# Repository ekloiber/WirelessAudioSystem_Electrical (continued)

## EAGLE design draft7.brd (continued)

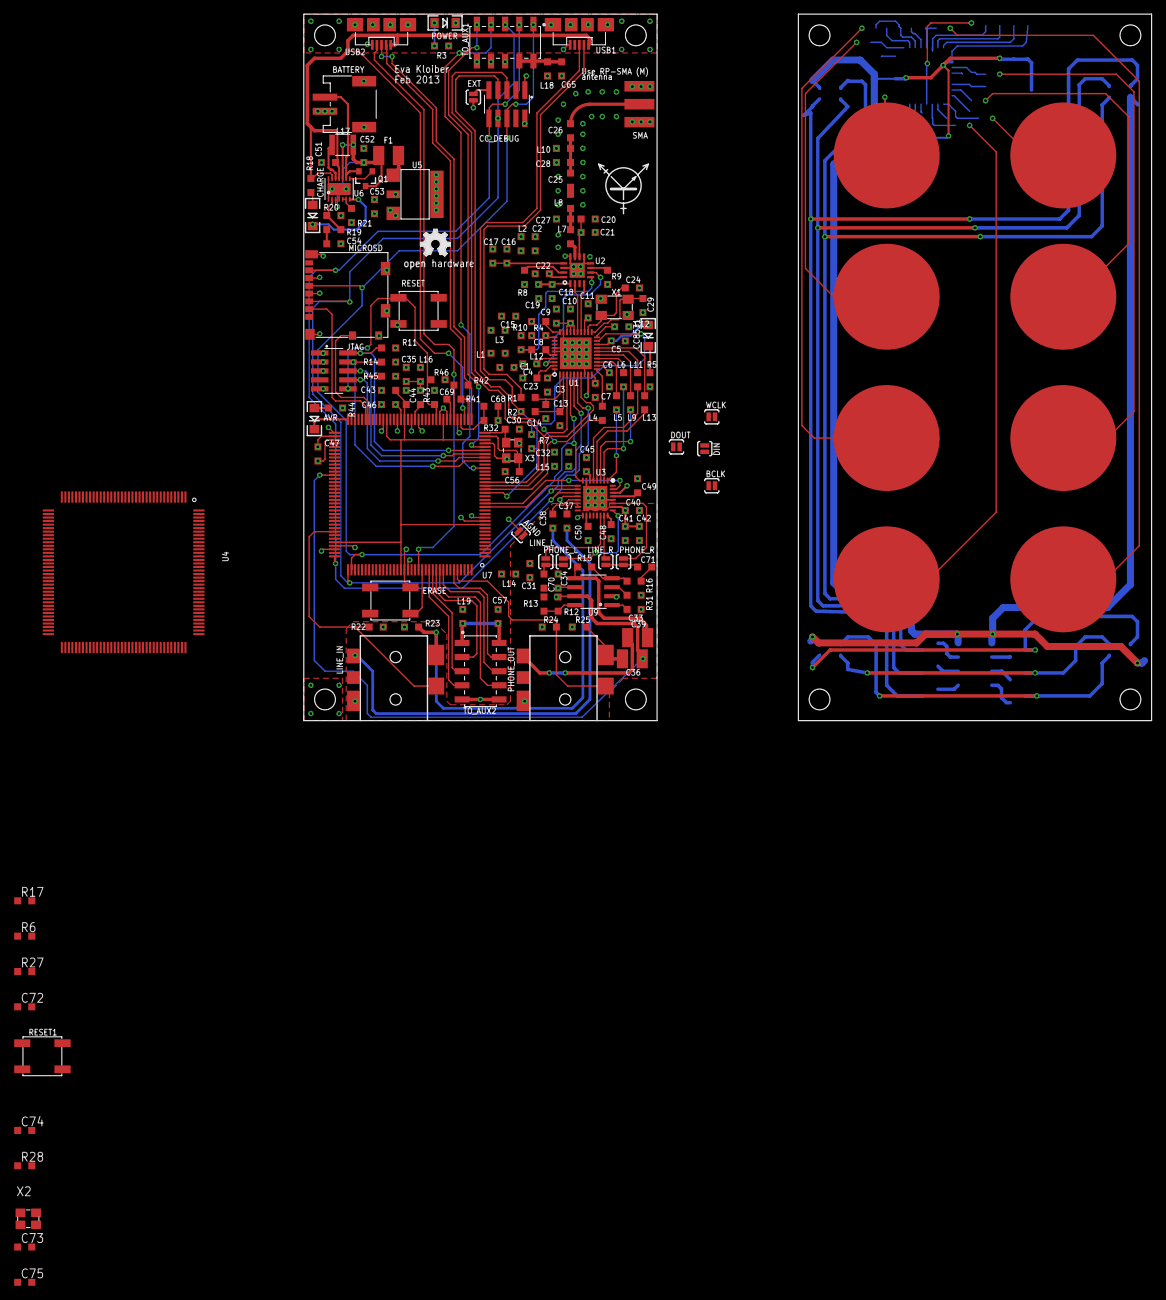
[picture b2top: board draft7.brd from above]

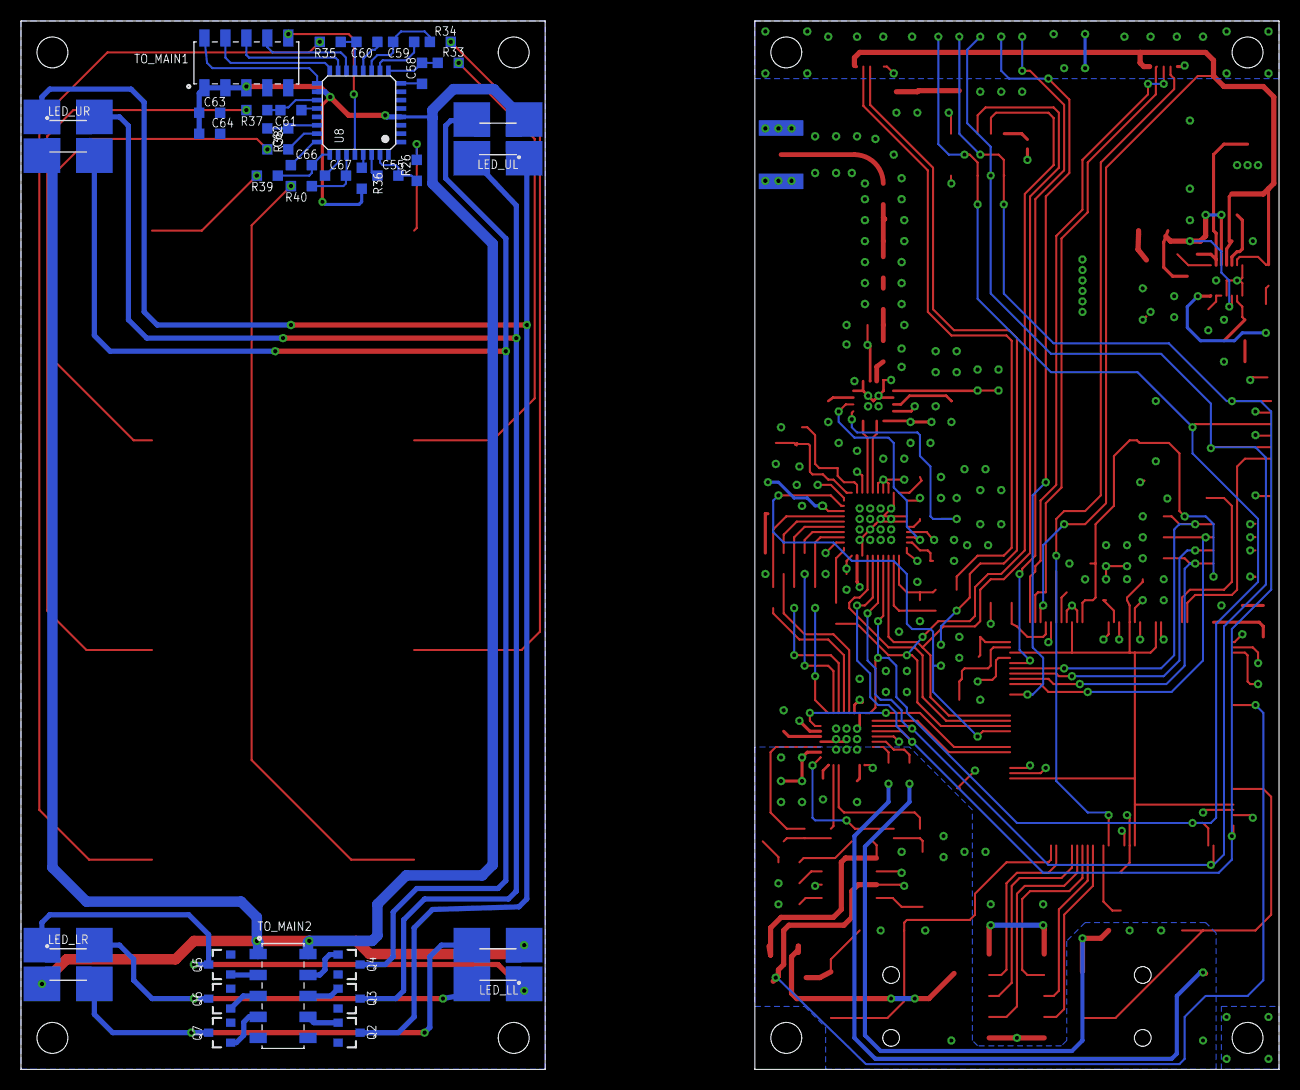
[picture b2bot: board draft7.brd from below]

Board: 4 copper layers, 120.0 x 100.0 mm, 214 parts (32 on the bottom side), 173 nets.

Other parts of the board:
U$1, U$5, U$6, U$7, U$8, U$11, U$12, U$13: STANDOFF_3/16
U$2, U$3: PHONE_PLUG
U$4, U$14: UBBP01
U$9: TRANS_SILK
U$10: OSHW_FILLX150_NOTEXT

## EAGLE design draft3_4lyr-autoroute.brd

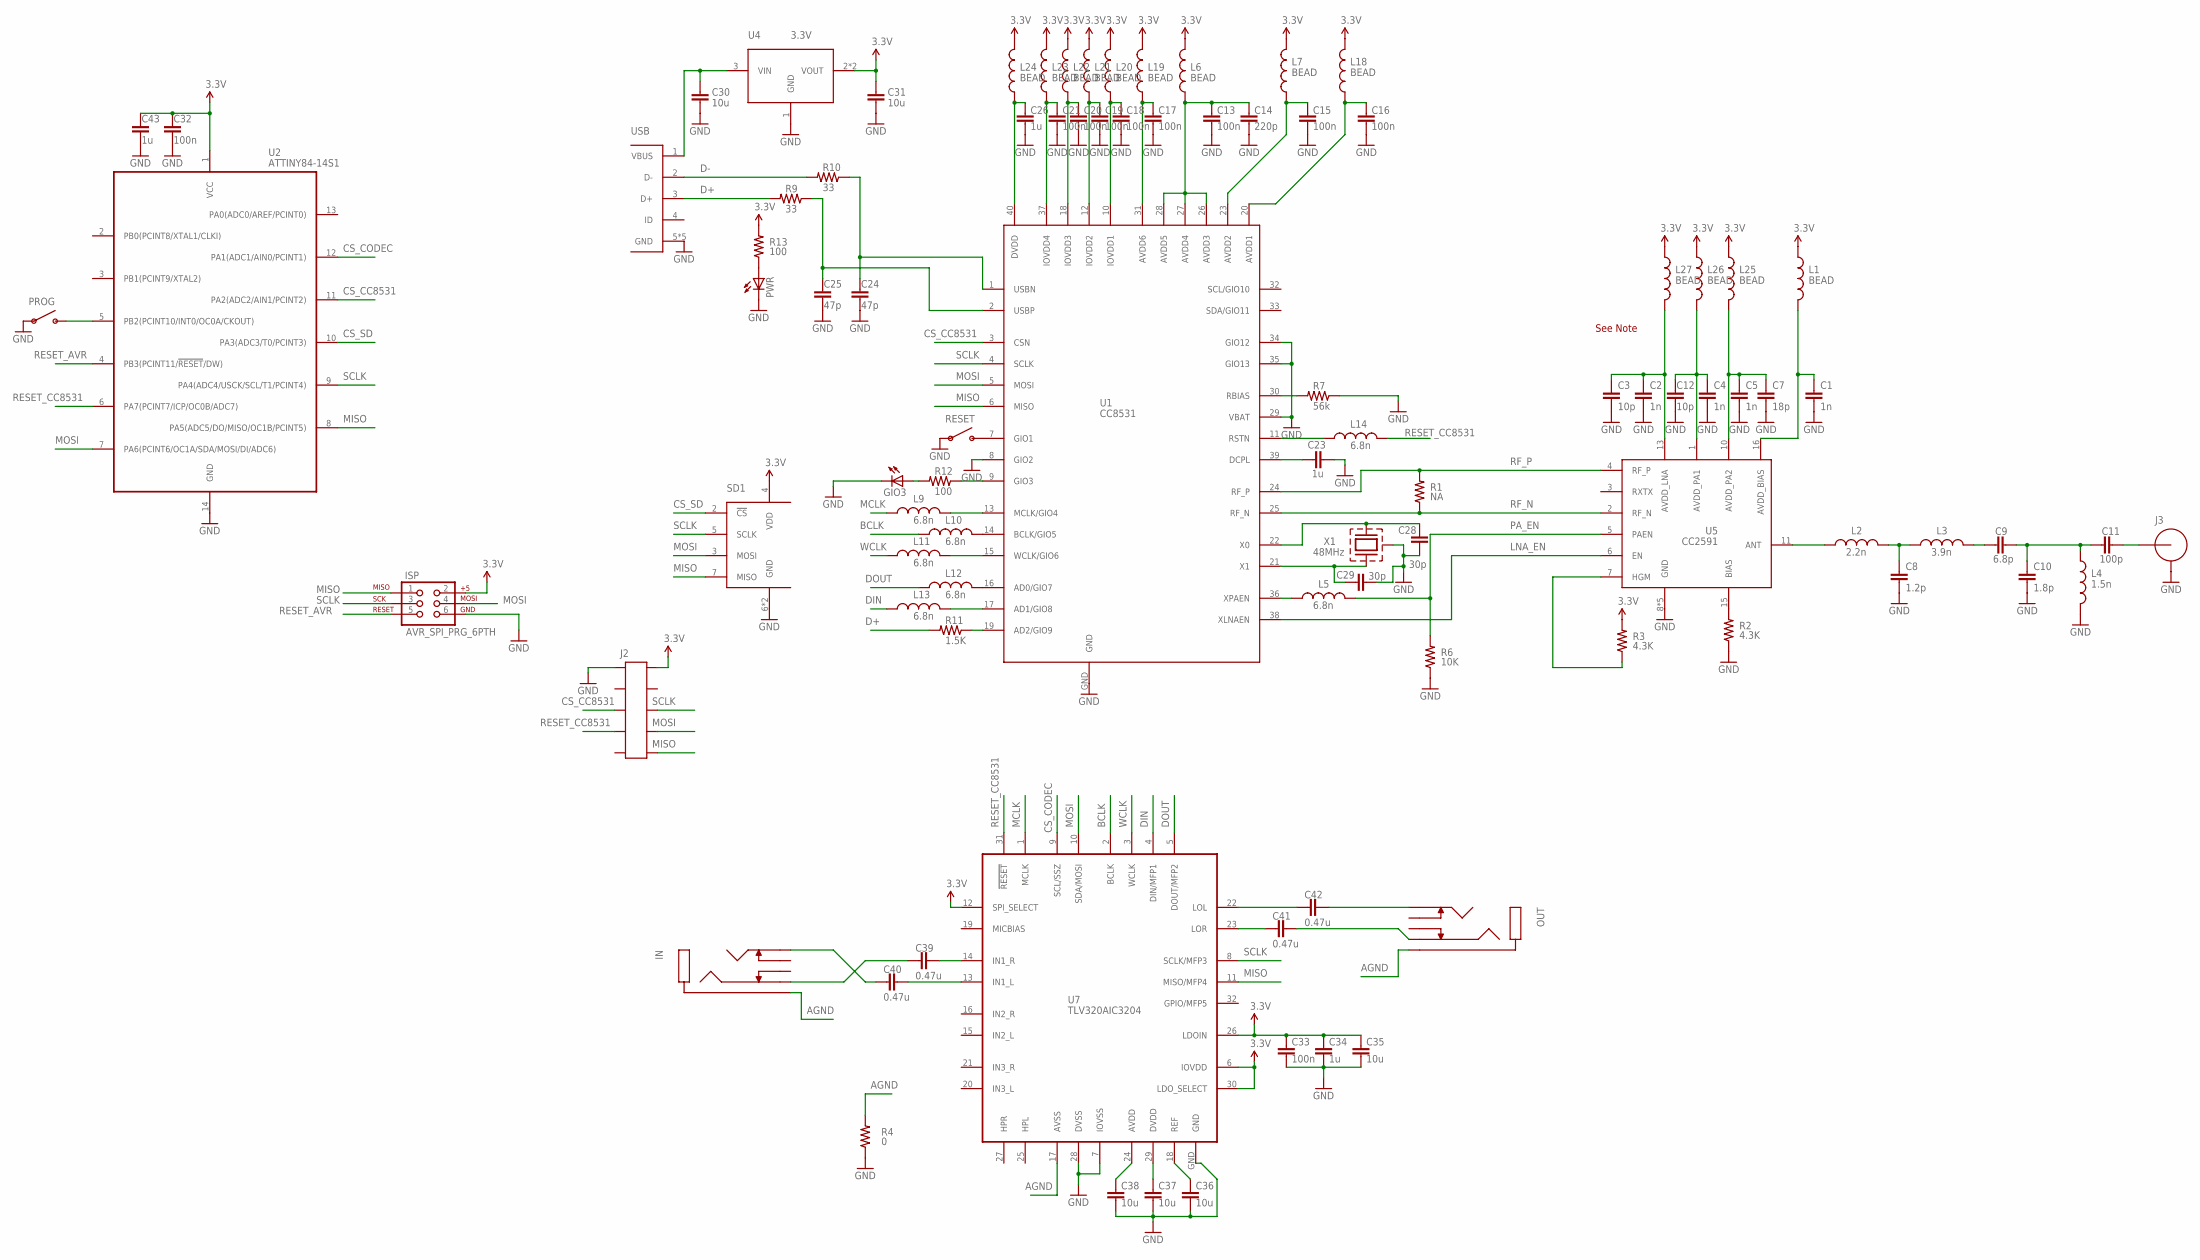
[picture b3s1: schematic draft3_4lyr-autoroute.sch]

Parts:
C1, C2, C4, C5: 1n; C0603
C3, C12: 10p; C0603
C7: 18p; C0603
C8: 1.2p; C0603
C9: 6.8p; C0603
C10: 1.8p; C0603
C11: 100p; C0603
C13, C15, C16, C17, C18, C19, C20, C21, C32, C33: 100n; C0603
C14: 220p; C0603
C23, C26, C34, C43: 1u; C0603
C24, C25: 47p; C0603
C28, C29: 30p; C0603
C30, C31, C35, C36, C37, C38: 10u; C0603
C39, C40, C41, C42: 0.47u; C0603
GIO3: LEDCHIP-LED0603; CHIP-LED0603
IN: PHONE_SW; 35RAPC4BV4
ISP: AVR_SPI_PRG_6PTH; 2X3
J2: HEADER-10P-SMD-MALE; 10P-0.05-HEADER
J3: SMA; CONSMA003.031
L1, L6, L7, L18, L19, L20, L21, L22, L23, L24, L25, L26, L27: BEAD; 0603
L2: 2.2n; 0603
L3: 3.9n; 0603
L4: 1.5n; 0603
L5, L9, L10, L11, L12, L13, L14: 6.8n; 0603
OUT: PHONE_SW; 35RAPC4BV4
PROG: SPST-SMD; TACT_SW
PWR: LEDCHIP-LED0603; CHIP-LED0603
R1: NA; R0603
R2, R3: 4.3K; R0603
R4: 0; R0603
R6: 10K; R0603
R7: 56k; R0603
R9, R10: 33; R0603
R11: 1.5K; R0603
R12, R13: 100; R0603
RESET: SPST-SMD; TACT_SW
SD1: MICROSDDM3AT; DM3AT
U1: CC8531; S-PVQFN-N40
U2: ATTINY84-14S1; SOIC14
U4: 3.3V; SOT-223
U5: CC2591; S-PVQFN-N16
U7: TLV320AIC3204; S-PVQFN-N32
USB: USB_MICRO_AB
X1: 48MHz; ABM3C

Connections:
3.3V: C31.1, C32.1, C33.1, C34.1, C35.1, C43.1, ISP.2, J2.2, L1.1, L6.2, L7.2, L18.2, L19.2, L20.2, L21.2, L22.2, L23.2, L24.2, L25.1, L26.1, L27.1, R3.2, R13.2, SD1.4 (VDD), U2.1 (VCC), U4.2 (VOUT), U4.4 (VOUT), U7.6 (IOVDD), U7.12 (SPI_SELECT), U7.26 (LDOIN), U7.30 (LDO_SELECT)
AGND: IN.1 (GND), OUT.1 (GND), R4.2, U7.17 (AVSS)
AVDD_BIAS: C1.1, L1.2, U5.16 (AVDD_BIAS)
AVDD_LNA: C2.1, C3.1, L27.2, U5.13 (AVDD_LNA)
AVDD_PA1: C4.1, C12.1, L26.2, U5.1 (AVDD_PA1)
AVDD_PA2: C5.1, C7.1, L25.2, U5.10 (AVDD_PA2)
BCLK: L10.1, U7.2 (BCLK)
CS_CC8531: J2.5, U1.3 (CSN), U2.11 (PA2(ADC2/AIN1/PCINT2))
CS_CODEC: U2.12 (PA1(ADC1/AIN0/PCINT1)), U7.9 (SCL/SSZ)
CS_SD: SD1.2 (!CS), U2.10 (PA3(ADC3/T0/PCINT3))
D+: R9.2, R11.2, USB.3 (D+)
D-: R10.2, USB.2 (D-)
DIN: L13.1, U7.4 (DIN/MFP1)
DOUT: L12.1, U7.5 (DOUT/MFP2)
GND: C1.2, C2.2, C3.2, C4.2, C5.2, C7.2, C8.2, C10.2, C12.2, C13.2, C14.2, C15.2, C16.2, C17.2, C18.2, C19.2, C20.2, C21.2, C23.2, C24.2, C25.2, C26.2, C28.2, C29.2, C30.2, C31.2, C32.2, C33.2, C34.2, C35.2, C36.2, C37.2, C38.2, C43.2, GIO3.C, ISP.6, J2.1, J3.GND1 (GND), J3.GND2 (GND), J3.GND3 (GND), J3.GND4 (GND), L4.2, PROG.1, PROG.2, PWR.C, R2.1, R4.1, R6.1, R7.1, RESET.1, RESET.2, SD1.6 (GND), SD1.GND, U1.8 (GIO2), U1.29 (VBAT), U1.34 (GIO12), U1.35 (GIO13), U1.GND, U2.14 (GND), U4.1 (GND), U5.8 (GND), U5.9 (GND), U5.12 (GND), U5.14 (GND), U5.GND, U7.7 (IOVSS), U7.28 (DVSS), U7.GND, USB.5 (GND), USB.GND1 (GND), USB.GND2 (GND), USB.GND3 (GND), USB.GND4 (GND), X1.2 (CASE), X1.4 (CASE)
IOVDD1: C24.1, R10.1, U1.1 (USBN)
IOVDD2: C25.1, R9.1, U1.2 (USBP)
LNA_EN: U1.38 (XLNAEN), U5.6 (EN)
MCLK: L9.1, U7.1 (MCLK)
MISO: ISP.1, J2.10, SD1.7 (MISO), U1.6 (MISO), U2.8 (PA5(ADC5/DO/MISO/OC1B/PCINT5)), U7.11 (MISO/MFP4)
MOSI: ISP.4, J2.8, SD1.3 (MOSI), U1.5 (MOSI), U2.7 (PA6(PCINT6/OC1A/SDA/MOSI/DI/ADC6)), U7.10 (SDA/MOSI)
unnamed: C29.1, U1.21 (X1), X1.1
unnamed: C28.1, U1.22 (X0), X1.3 (2)
unnamed: L14.1, U1.11 (RSTN)
unnamed: PROG.3, PROG.4, U2.5 (PB2(PCINT10/INT0/OC0A/CKOUT))
unnamed: L10.2, U1.14 (BCLK/GIO5)
unnamed: C30.1, U4.3 (VIN), USB.1 (VBUS)
unnamed: R2.2, U5.15 (BIAS)
unnamed: R3.1, U5.7 (HGM)
unnamed: C11.2, J3.SIG
unnamed: L12.2, U1.16 (AD0/GIO7)
unnamed: RESET.3, RESET.4, U1.7 (GIO1)
unnamed: C38.1, U7.24 (AVDD)
unnamed: L2.1, U5.11 (ANT)
unnamed: C8.1, L2.2, L3.1
unnamed: C9.1, L3.2
unnamed: C9.2, C10.1, C11.1, L4.1
unnamed: C13.1, C14.1, L6.1, U1.26 (AVDD3), U1.27 (AVDD4), U1.28 (AVDD5)
unnamed: L5.1, U1.36 (XPAEN)
unnamed: R7.2, U1.30 (RBIAS)
unnamed: C36.1, U7.18 (REF)
unnamed: C23.1, U1.39 (DCPL)
unnamed: C15.1, L7.1, U1.23 (AVDD2)
unnamed: L9.2, U1.13 (MCLK/GIO4)
unnamed: R11.1, U1.19 (AD2/GIO9)
unnamed: L11.2, U1.15 (WCLK/GIO6)
unnamed: C16.1, L18.1, U1.20 (AVDD1)
unnamed: L13.2, U1.17 (AD1/GIO8)
unnamed: R12.1, U1.9 (GIO3)
unnamed: GIO3.A, R12.2
unnamed: C17.1, L19.1, U1.31 (AVDD6)
unnamed: PWR.A, R13.1
unnamed: C37.1, U7.29 (DVDD)
unnamed: C40.1, IN.2 (L)
unnamed: C39.2, U7.14 (IN1_R)
unnamed: C40.2, U7.13 (IN1_L)
unnamed: C39.1, IN.4 (R)
unnamed: C42.2, OUT.2 (L)
unnamed: C41.2, OUT.4 (R)
unnamed: C42.1, U7.22 (LOL)
unnamed: C41.1, U7.23 (LOR)
unnamed: C18.1, L20.1, U1.10 (IOVDD1)
unnamed: C19.1, L21.1, U1.12 (IOVDD2)
unnamed: C20.1, L22.1, U1.18 (IOVDD3)
unnamed: C21.1, L23.1, U1.37 (IOVDD4)
unnamed: C26.1, L24.1, U1.40 (DVDD)
PA_EN: L5.2, R6.2, U5.5 (PAEN)
RESET_AVR: ISP.5, U2.4 (PB3(PCINT11/!RESET!/DW))
RESET_CC8531: J2.7, L14.2, U2.6 (PA7(PCINT7/ICP/OC0B/ADC7)), U7.31 (!RESET)
RF_N: R1.1, U1.25 (RF_N), U5.2 (RF_N)
RF_P: R1.2, U1.24 (RF_P), U5.4 (RF_P)
SCLK: ISP.3, J2.6, SD1.5 (SCLK), U1.4 (SCLK), U2.9 (PA4(ADC4/USCK/SCL/T1/PCINT4)), U7.8 (SCLK/MFP3)
WCLK: L11.1, U7.3 (WCLK)

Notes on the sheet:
See Note

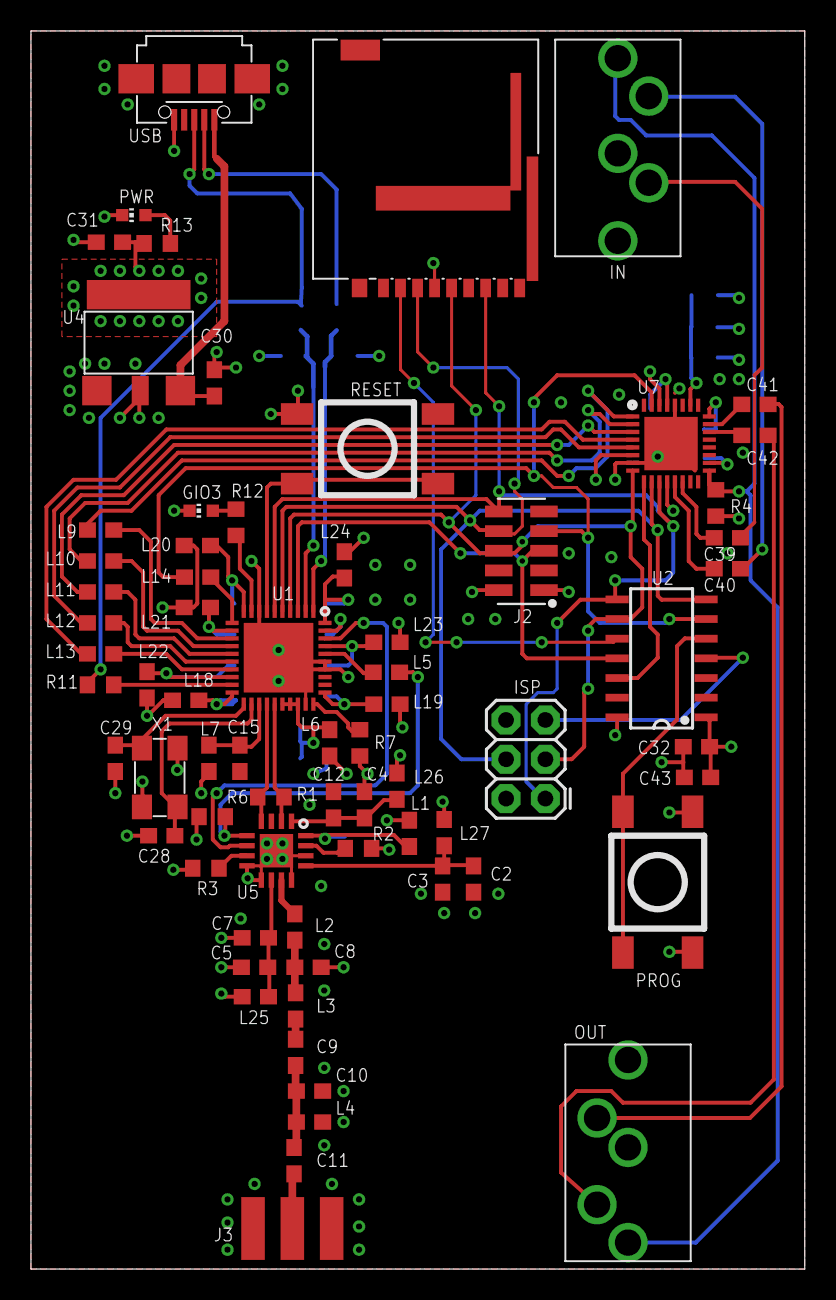
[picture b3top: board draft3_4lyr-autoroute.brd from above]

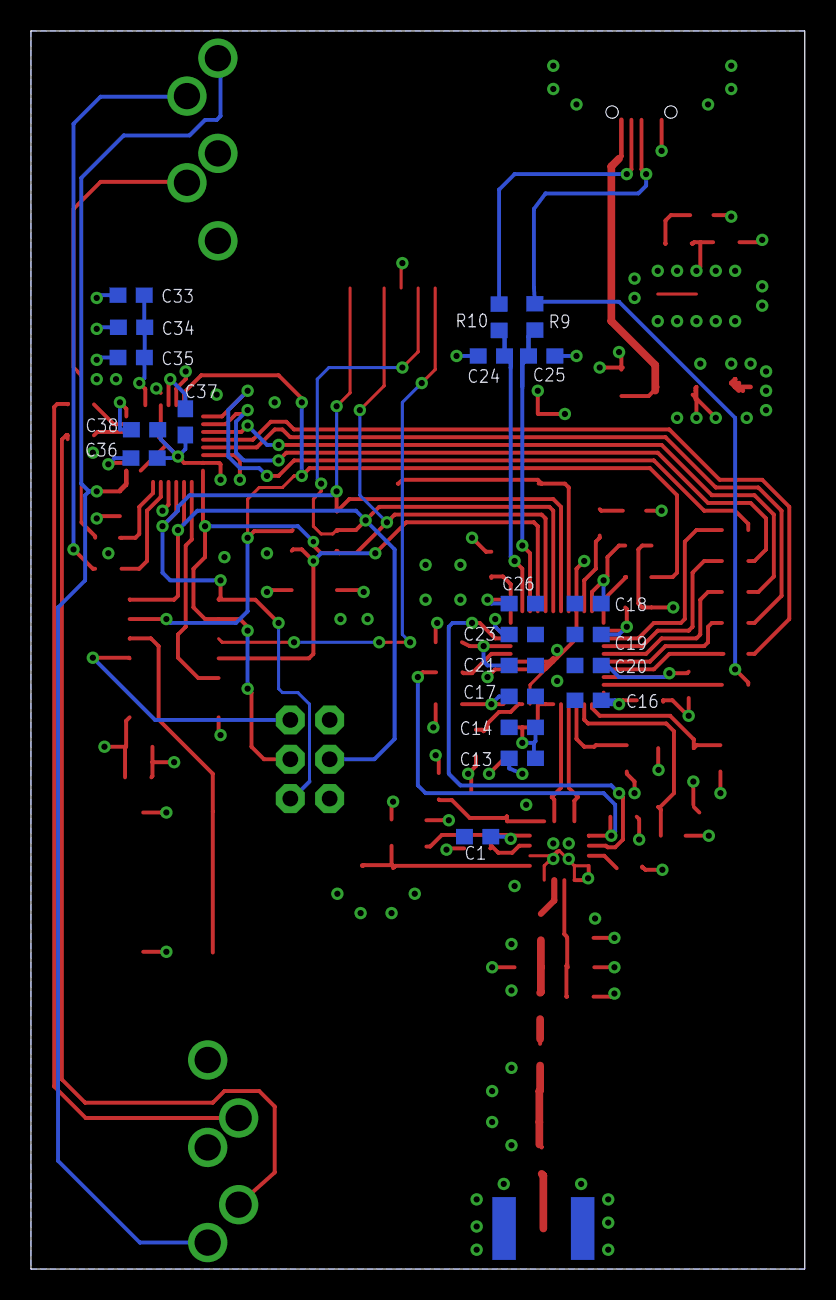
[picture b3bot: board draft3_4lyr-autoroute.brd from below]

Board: 4 copper layers, 50.0 x 80.0 mm, 91 parts (21 on the bottom side), 73 nets.

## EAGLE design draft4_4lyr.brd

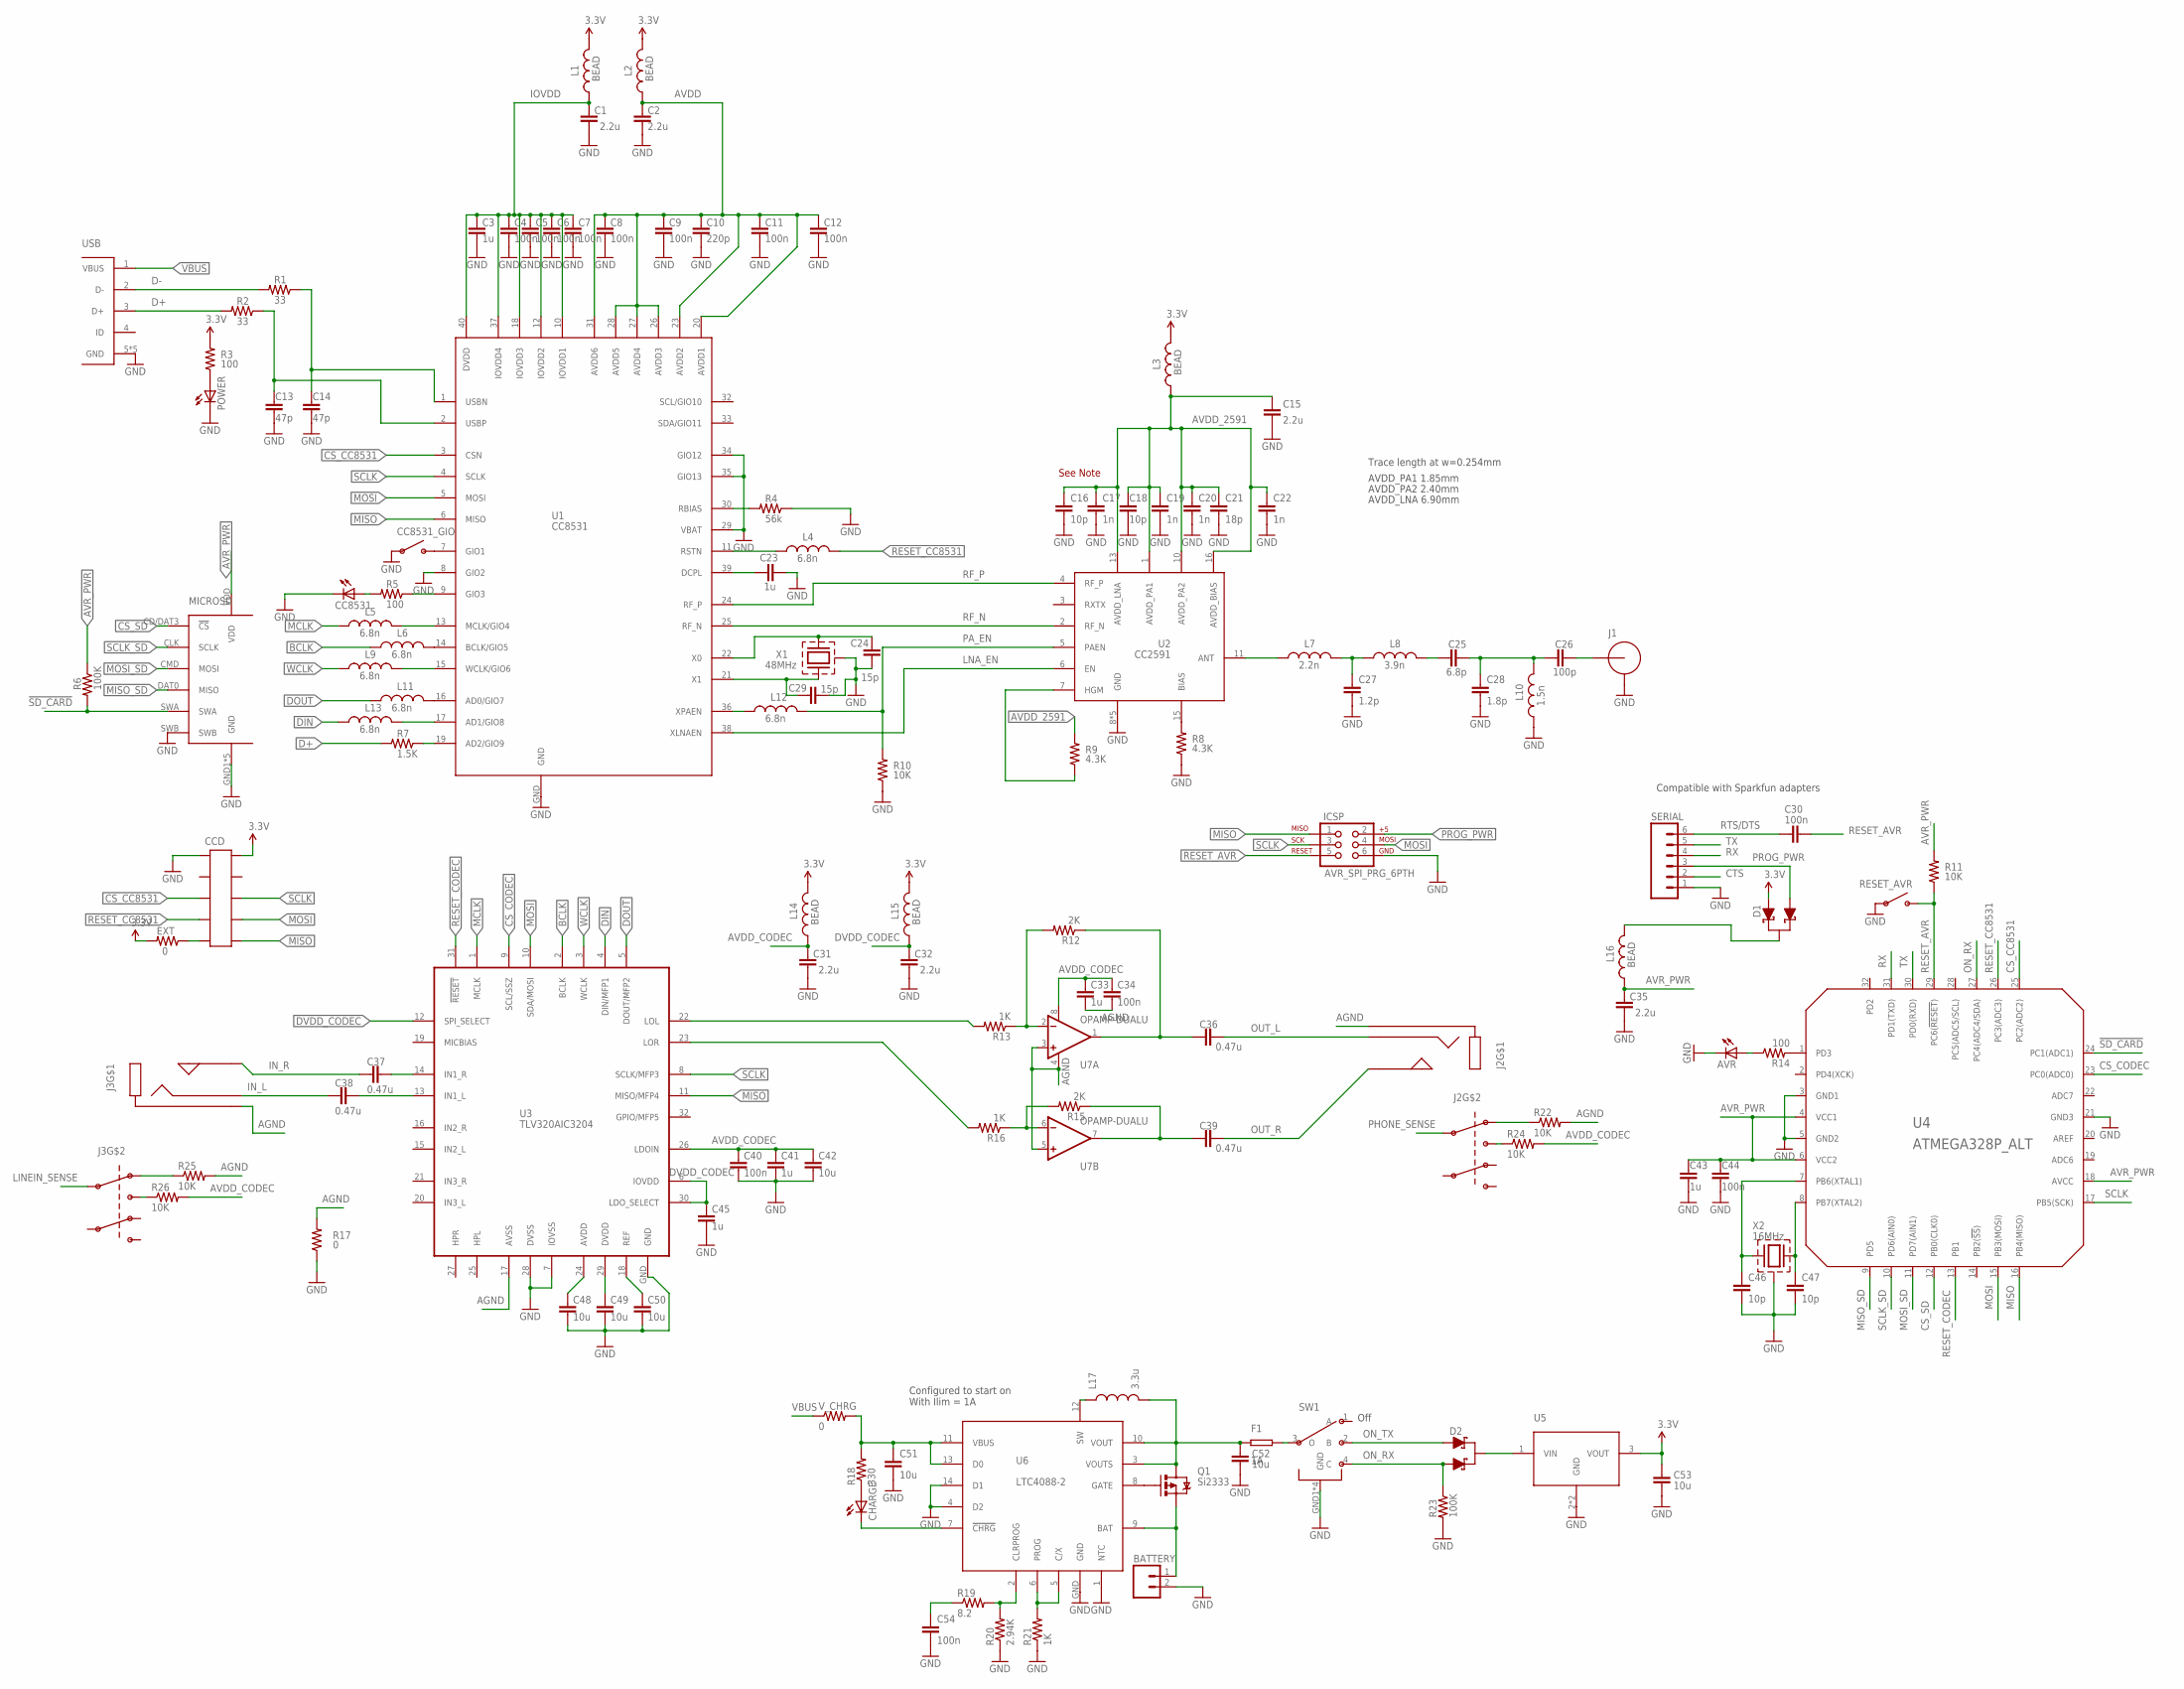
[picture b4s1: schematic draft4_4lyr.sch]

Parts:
AVR: LED1206; LED-1206
BATTERY: M02-JST-2MM-SMT; JST-2-SMD
C1, C2, C15, C31, C32, C35: 2.2u; C0603
C3, C23, C33, C41, C43, C45: 1u; C0603
C4, C5, C6, C7, C8, C9, C11, C12, C30, C34, C40, C44, C54: 100n; C0603
C10: 220p; C0603
C13, C14: 47p; C0603
C16, C18, C46, C47: 10p; C0603
C17, C19, C20, C22: 1n; C0603
C21: 18p; C0603
C24, C29: 15p; C0603
C25: 6.8p; C0603
C26: 100p; C0603
C27: 1.2p; C0603
C28: 1.8p; C0603
C36, C37, C38, C39: 0.47u; C0603
C42, C48, C49, C50, C51, C52, C53: 10u; C0603
CC8531: LED1206; LED-1206
CC8531_GIO: SPST-SMD; TACT_SW
CCD: HEADER-10P-PTH-MALE; 2X5
CHARGE: LED1206; LED-1206
D1, D2: DUAL_SCHOTTKY; SOT-23
EXT: 0; R0603
F1: 1A; 1210
ICSP: AVR_SPI_PRG_6PTH; 2X3
J1: SMA; CONSMA003.031
J2, J3: PHONE_DPDT; STX-3100-9N
L1, L2, L3, L14, L15, L16: BEAD; 0603
L4, L5, L6, L9, L11, L12, L13: 6.8n; 0603
L7: 2.2n; 0603
L8: 3.9n; 0603
L10: 1.5n; 0603
L17: 3.3u; IFSC-1111AB-01
MICROSD: MICROSD104031-0811; MOLEX_104031-0811
POWER: LED1206; LED-1206
Q1: Si2333; SOT23-3
R1, R2: 33; R0603
R3, R5, R14: 100; R0603
R4: 56k; R0603
R6, R23: 100K; R0603
R7: 1.5K; R0603
R8, R9: 4.3K; R0603
R10, R11, R22, R24, R25, R26: 10K; R0603
R12, R15: 2K; R0603
R13, R16, R21: 1K; R0603
R17: 0; R0603
R18: 330; R0603
R19: 8.2; R0603
R20: 2.94K; R0603
RESET_AVR: SPST-SMD; TACT_SW
SERIAL: M06SIP; 1X06
SW1: SP3T-SSSS812201; SSSS812201
U1: CC8531; S-PVQFN-N40
U2: CC2591; S-PVQFN-N16
U3: TLV320AIC3204; S-PVQFN-N32
U4: ATMEGA328P_ALT; S-PQFP-N32
U5: MCP1826-SOT223; SOT-223
U6: LTC4088-2; DFN-14
U7: OPAMP-DUALU; SO08
USB: USB_MICRO_AB
V_CHRG: 0; R0603
X1: 48MHz; ABM3C
X2: 16MHz; ABM8G

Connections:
3.3V: C53.1, CCD.2, D1.1 (A1), EXT.2, L1.2, L2.2, L3.2, L14.2, L15.2, R3.2, U5.3 (VOUT)
!SD_CARD: MICROSD.SWA, R6.2, U4.24 (PC1(ADC1))
AGND: C33.2, C34.2, J2.1 (GND), J3.1 (GND), R17.2, R22.2, R25.2, U3.17 (AVSS), U7.3 (+IN), U7.4 (V-), U7.5 (+IN)
AVDD: C2.1, C8.1, C9.1, C10.1, C11.1, C12.1, L2.1, U1.20 (AVDD1), U1.23 (AVDD2), U1.26 (AVDD3), U1.27 (AVDD4), U1.28 (AVDD5), U1.31 (AVDD6)
AVDD_2591: C15.1, C16.1, C17.1, C18.1, C19.1, C20.1, C21.1, C22.1, L3.1, R9.2, U2.1 (AVDD_PA1), U2.10 (AVDD_PA2), U2.13 (AVDD_LNA), U2.16 (AVDD_BIAS)
AVDD_CODEC: C31.1, C33.1, C34.1, C40.1, C41.1, C42.1, L14.1, R24.2, R26.2, U3.26 (LDOIN), U7.8 (V+)
AVR_PWR: C35.1, C43.1, C44.1, L16.1, MICROSD.VDD, R6.1, R11.2, U4.4 (VCC1), U4.6 (VCC2), U4.18 (AVCC)
BAT: BATTERY.1 (2), Q1.2 (S), U6.9 (BAT)
BCLK: L6.1, U3.2 (BCLK)
CS_CC8531: CCD.5, U1.3 (CSN), U4.25 (PC2(ADC2))
CS_CODEC: U3.9 (SCL/SSZ), U4.23 (PC0(ADC0))
CS_SD: MICROSD.CD/DAT3 (!CS), U4.12 (PB0(CLK0))
CTS: SERIAL.2
D+: R2.2, R7.2, USB.3 (D+)
D-: R1.2, USB.2 (D-)
DIN: L13.1, U3.4 (DIN/MFP1)
DOUT: L11.1, U3.5 (DOUT/MFP2)
DVDD: C49.1, U3.29 (DVDD)
DVDD_CODEC: C32.1, C45.1, L15.1, U3.6 (IOVDD), U3.12 (SPI_SELECT), U3.30 (LDO_SELECT)
GND: AVR.C, BATTERY.2 (1), C1.2, C2.2, C3.2, C4.2, C5.2, C6.2, C7.2, C8.2, C9.2, C10.2, C11.2, C12.2, C13.2, C14.2, C15.2, C16.2, C17.2, C18.2, C19.2, C20.2, C21.2, C22.2, C23.2, C24.2, C27.2, C28.2, C29.2, C31.2, C32.2, C35.2, C40.2, C41.2, C42.2, C43.2, C44.2, C45.2, C46.2, C47.2, C48.2, C49.2, C50.2, C51.2, C52.2, C53.2, C54.2, CC8531.C, CC8531_GIO.1, CC8531_GIO.2, CCD.1, ICSP.6, J1.GND1 (GND), J1.GND2 (GND), J1.GND3 (GND), J1.GND4 (GND), L10.1, MICROSD.GND1 (GND), MICROSD.GND2 (GND), MICROSD.GND3 (GND), MICROSD.GND4 (GND), MICROSD.SWB, MICROSD.VSS (GND), POWER.C, R4.1, R8.1, R10.1, R17.1, R20.1, R21.1, R23.2, RESET_AVR.1, RESET_AVR.2, SERIAL.1, SW1.GND1 (GND), SW1.GND2 (GND), SW1.GND3 (GND), SW1.GND4 (GND), U1.8 (GIO2), U1.29 (VBAT), U1.34 (GIO12), U1.35 (GIO13), U1.GND, U2.8 (GND), U2.9 (GND), U2.12 (GND), U2.14 (GND), U2.GND, U3.7 (IOVSS), U3.28 (DVSS), U3.GND, U4.3 (GND1), U4.5 (GND2), U4.21 (GND3), U5.2 (GND), U5.4 (GND), U6.1 (NTC), U6.4 (D2), U6.14 (D1), U6.GND, USB.5 (GND), USB.GND1 (GND), USB.GND2 (GND), USB.GND3 (GND), USB.GND4 (GND), X1.2 (CASE), X1.4 (CASE), X2.GND-1 (CASE), X2.GND-2 (CASE)
IN_L: C38.1, J3.3 (R)
IN_R: C37.1, J3.2 (L)
IOVDD: C1.1, C3.1, C4.1, C5.1, C6.1, C7.1, L1.1, U1.10 (IOVDD1), U1.12 (IOVDD2), U1.18 (IOVDD3), U1.37 (IOVDD4), U1.40 (DVDD)
IOVDD1: C14.1, R1.1, U1.1 (USBN)
IOVDD2: C13.1, R2.1, U1.2 (USBP)
LINEIN_SENSE: J3.7 (S1)
LNA_EN: U1.38 (XLNAEN), U2.6 (EN)
MCLK: L5.1, U3.1 (MCLK)
MISO: CCD.10, ICSP.1, U1.6 (MISO), U3.11 (MISO/MFP4), U4.16 (PB4(MISO))
MISO_SD: MICROSD.DAT0 (MISO), U4.9 (PD5)
MOSI: CCD.8, ICSP.4, U1.5 (MOSI), U3.10 (SDA/MOSI), U4.15 (PB3(MOSI))
MOSI_SD: MICROSD.CMD (MOSI), U4.11 (PD7(AIN1))
unnamed: C29.1, U1.21 (X1), X1.1
unnamed: C24.1, U1.22 (X0), X1.3 (2)
unnamed: L4.1, U1.11 (RSTN)
unnamed: L11.2, U1.16 (AD0/GIO7)
unnamed: L6.2, U1.14 (BCLK/GIO5)
unnamed: D1.3 (C1), L16.2
unnamed: R8.2, U2.15 (BIAS)
unnamed: R9.1, U2.7 (HGM)
unnamed: C26.2, J1.SIG
unnamed: D2.3 (C1), U5.1 (VIN)
unnamed: CC8531_GIO.3, CC8531_GIO.4, U1.7 (GIO1)
unnamed: C46.1, U4.7 (PB6(XTAL1)), X2.X1 (1)
unnamed: L7.1, U2.11 (ANT)
unnamed: C27.1, L7.2, L8.1
unnamed: C25.1, L8.2
unnamed: C25.2, C26.1, C28.1, L10.2
unnamed: C48.1, U3.24 (AVDD)
unnamed: L12.1, U1.36 (XPAEN)
unnamed: R4.2, U1.30 (RBIAS)
unnamed: C47.1, U4.8 (PB7(XTAL2)), X2.X2 (2)
unnamed: C23.1, U1.39 (DCPL)
unnamed: F1.2, SW1.3 (O)
unnamed: L5.2, U1.13 (MCLK/GIO4)
unnamed: R7.1, U1.19 (AD2/GIO9)
unnamed: L9.2, U1.15 (WCLK/GIO6)
unnamed: J2.6 (S1-NC), R22.1
unnamed: L13.2, U1.17 (AD1/GIO8)
unnamed: R5.1, U1.9 (GIO3)
unnamed: CC8531.A, R5.2
unnamed: J2.8 (S1-NO), R24.1
unnamed: POWER.A, R3.1
unnamed: CHARGE.C, U6.7 (!CHRG)
unnamed: CHARGE.A, R18.1
unnamed: C37.2, U3.14 (IN1_R)
unnamed: C38.2, U3.13 (IN1_L)
unnamed: L17.1, U6.12 (SW)
unnamed: R21.2, U6.5 (C/X), U6.6 (PROG)
unnamed: R19.2, R20.2, U6.2 (CLRPROG)
unnamed: C36.1, R12.1, U7.1 (OUT)
unnamed: C39.1, R15.1, U7.7 (OUT)
unnamed: J3.6 (S1-NC), R25.1
unnamed: J3.8 (S1-NO), R26.1
unnamed: R14.2, U4.1 (PD3)
unnamed: AVR.A, R14.1
unnamed: C54.1, R19.1
unnamed: C52.1, F1.1, L17.2, Q1.3 (D), U6.3 (VOUTS), U6.10 (VOUT)
unnamed: CCD.9, EXT.1
unnamed: Q1.1 (G), U6.8 (GATE)
unnamed: C51.1, R18.2, U6.11 (VBUS), U6.13 (D0), V_CHRG.2
unnamed: R12.2, R13.1, U7.2 (-IN)
unnamed: R15.2, R16.1, U7.6 (-IN)
unnamed: R13.2, U3.22 (LOL)
unnamed: R16.2, U3.23 (LOR)
ON_RX: D2.2 (A), R23.1, SW1.4 (C), U4.27 (PC4(ADC4/SDA))
ON_TX: D2.1 (A1), SW1.2 (B)
OUT_L: C36.2, J2.3 (R)
OUT_R: C39.2, J2.2 (L)
PA_EN: L12.2, R10.2, U2.5 (PAEN)
PHONE_SENSE: J2.7 (S1)
PROG_PWR: D1.2 (A), ICSP.2, SERIAL.3
REF: C50.1, U3.18 (REF)
RESET_AVR: C30.2, ICSP.5, R11.1, RESET_AVR.3, RESET_AVR.4, U4.29 (PC6(!RESET!))
RESET_CC8531: CCD.7, L4.2, U4.26 (PC3(ADC3))
RESET_CODEC: U3.31 (!RESET), U4.13 (PB1)
RF_N: U1.25 (RF_N), U2.2 (RF_N)
RF_P: U1.24 (RF_P), U2.4 (RF_P)
RTS/DTS: C30.1, SERIAL.6
RX: SERIAL.4, U4.31 (PD1(TXD))
SCLK: CCD.6, ICSP.3, U1.4 (SCLK), U3.8 (SCLK/MFP3), U4.17 (PB5(SCK))
SCLK_SD: MICROSD.CLK (SCLK), U4.10 (PD6(AIN0))
TX: SERIAL.5, U4.30 (PD0(RXD))
VBUS: USB.1 (VBUS), V_CHRG.1
WCLK: L9.1, U3.3 (WCLK)

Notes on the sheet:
See Note
Compatible with Sparkfun adapters
AVDD_PA1 1.85mm
AVDD_PA2 2.40mm
AVDD_LNA 6.90mm
Trace length at w=0.254mm
Off
Configured to start on With Ilim = 1A

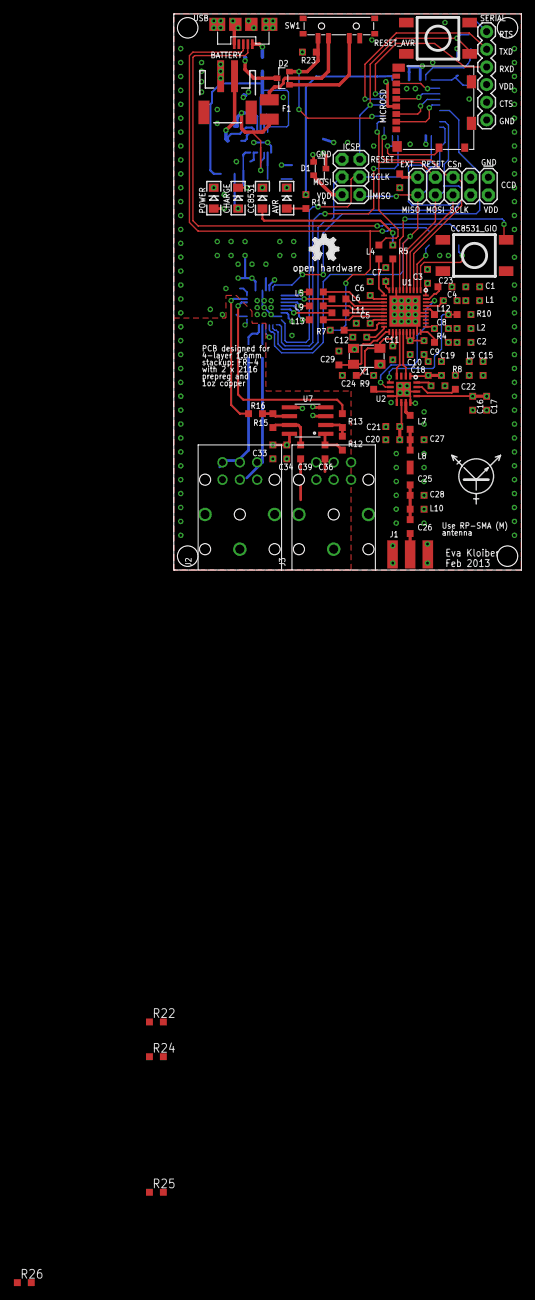
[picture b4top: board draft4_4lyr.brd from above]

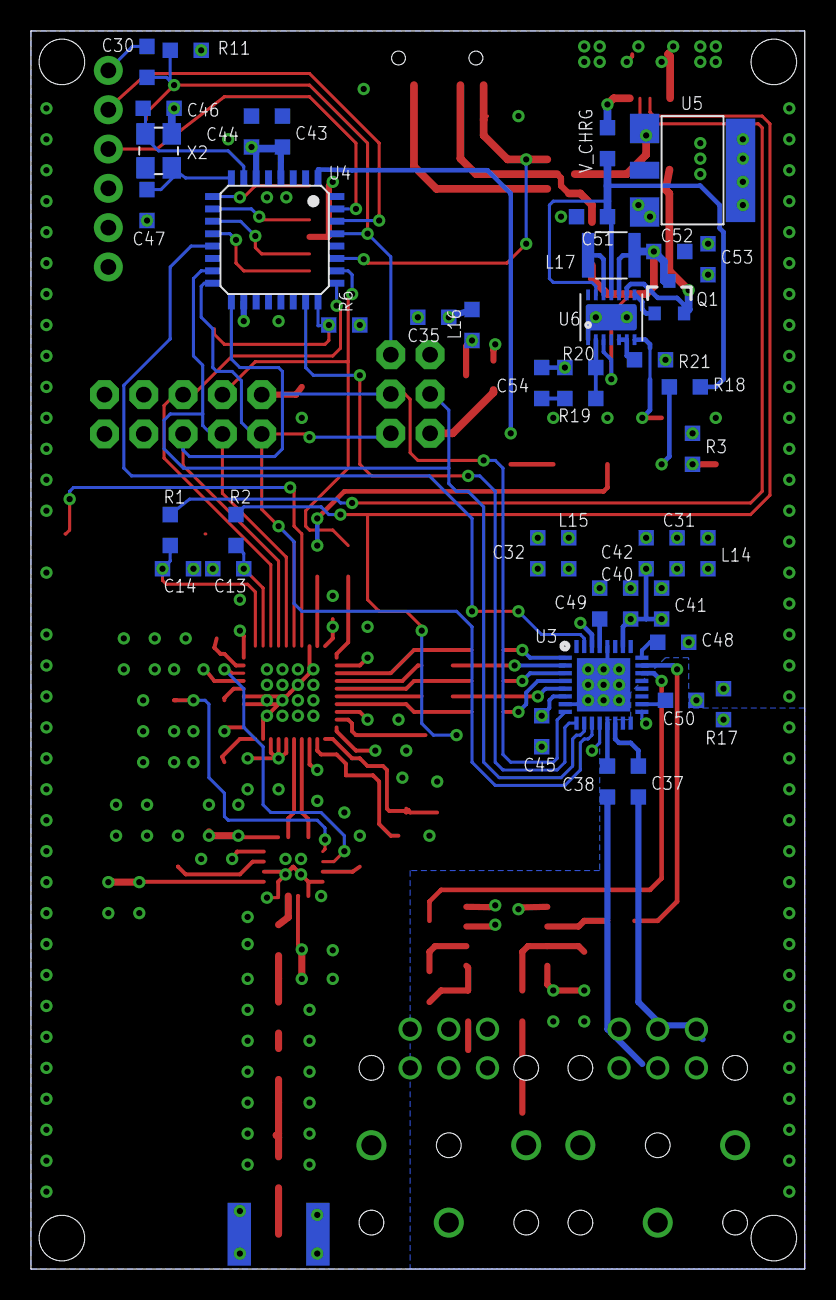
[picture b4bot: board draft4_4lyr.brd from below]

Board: 4 copper layers, 50.0 x 80.0 mm, 137 parts (44 on the bottom side), 102 nets.

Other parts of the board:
U$1, U$5, U$6, U$7: HOLE_4-40
U$2, U$3: PHONE_PLUG
U$4: MICROSD
U$9: TRANS_SILK
U$10: OSHW_FILLX150_NOTEXT

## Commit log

2013-03-20 Initial files
2013-03-20 Deleted old files
2013-03-21 Messed around with stuff
2013-03-21 Added ignore files
2013-03-21 Added JTAG header
2013-03-21 Added USB enumeration sense
2013-03-23 Added I2S support for microcontroller
2013-03-23 Revert "Added I2S support for microcontroller"
    This reverts commit 61ee5d3334bc31ec9c7f427f77077646301e58fd.
2013-03-23 Fixed stuff, created prototype board
2013-03-26 New revision, changed proto board
2013-03-26 Board layout work
2013-03-27 Switched to AT32UC3A3
2013-03-28 New schematic - added new codec, clocking, etc
2013-03-28 Layout work
2013-03-29 More layout work
2013-04-08 Did a whole lot of things
2013-04-09 Minor revisions
2013-04-30 More revisions
    Added NAND and SDRAM memories
2013-05-07 PCB work
    Routed SDRAM, removed NAND
